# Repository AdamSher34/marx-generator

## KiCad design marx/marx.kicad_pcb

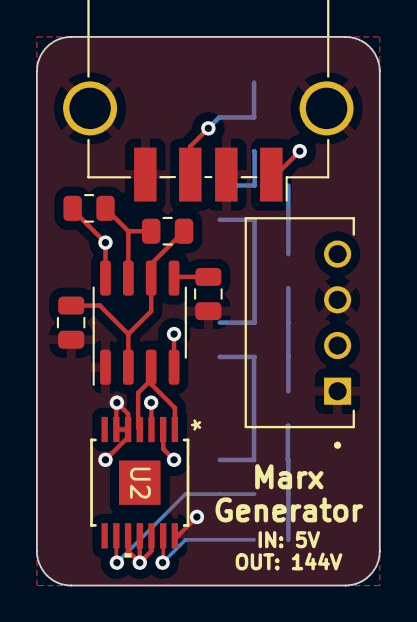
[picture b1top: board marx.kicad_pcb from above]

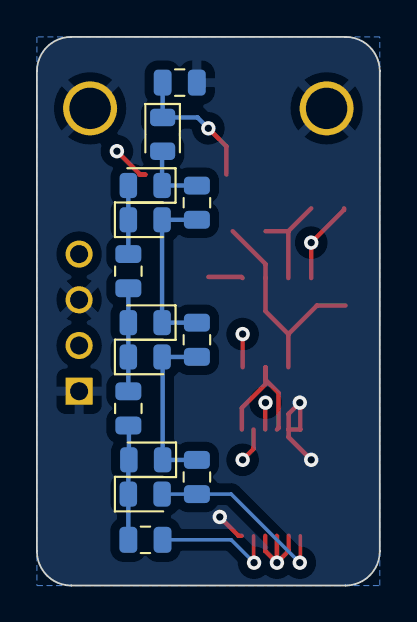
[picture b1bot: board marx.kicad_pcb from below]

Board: 4 copper layers, 19.1 x 30.5 mm, 22 parts (14 on the bottom side), 16 nets.

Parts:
C1, C2, C3, C4, C5, C6, C7: 10u; C_0805_2012Metric
C8: 10n; C_0805_2012Metric
C9: 27n; C_0805_2012Metric
D1, D2, D3, D4, D5, D6, D7: D_Schottky; D_0805_2012Metric
J1: USB_A; USB_A_TE_292303-7_Horizontal
R1: 1K; R_0805_2012Metric
R2: 100K; R_0805_2012Metric
U1: NA555D; SOIC-8_3.9x4.9mm_P1.27mm
U2: ALM2403QPWPRQ1; ALM2403QPWPRQ1_TEX
VR1: PDSE1-S5-S24-S; CONV_PDSE1-S5-S24-S

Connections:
+5V: J1.1 (VBUS), R1.1, U1.4 (R), U1.8 (VCC), U2.2 (IN1+), VR1.2 (VIN)
+24V: U2.3 (OTF/NRST), U2.10 (V+), U2.11 (V+), U2.12 (V+), VR1.4 (+VOUT)
/BOOST: C7.1, D7.1 (K), J1.3 (D+)
/Oscillator/CLK: U1.3 (Q), U2.1 (IN1-), U2.4 (IN2+)
/Oscillator/OSC+: C1.1, U2.13 (OUT1)
/Oscillator/OSC-: C2.1, D1.2 (A), U2.9 (OUT2)
/Oscillator/TRIG: C9.2, R2.2, U1.2 (TR), U1.6 (THR)
GND: C7.2, C8.2, C9.1, J1.2 (D-), J1.4 (GND), J1.5 (Shield), U1.1 (GND), U2.5 (IN2-), U2.6 (V-), U2.14 (V-), VR1.1 (GND), VR1.3 (0V)
unnamed: C1.2, C3.1, D1.1 (K), D2.2 (A)
unnamed: C2.2, C4.1, D2.1 (K), D3.2 (A)
unnamed: C3.2, C5.1, D3.1 (K), D4.2 (A)
unnamed: C4.2, C6.1, D4.1 (K), D5.2 (A)
unnamed: C5.2, D5.1 (K), D6.2 (A)
unnamed: C6.2, D6.1 (K), D7.2 (A)
unnamed: C8.1, U1.5 (CV)
unnamed: R1.2, R2.1, U1.7 (DIS)

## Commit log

2024-03-14 schematic and layout
